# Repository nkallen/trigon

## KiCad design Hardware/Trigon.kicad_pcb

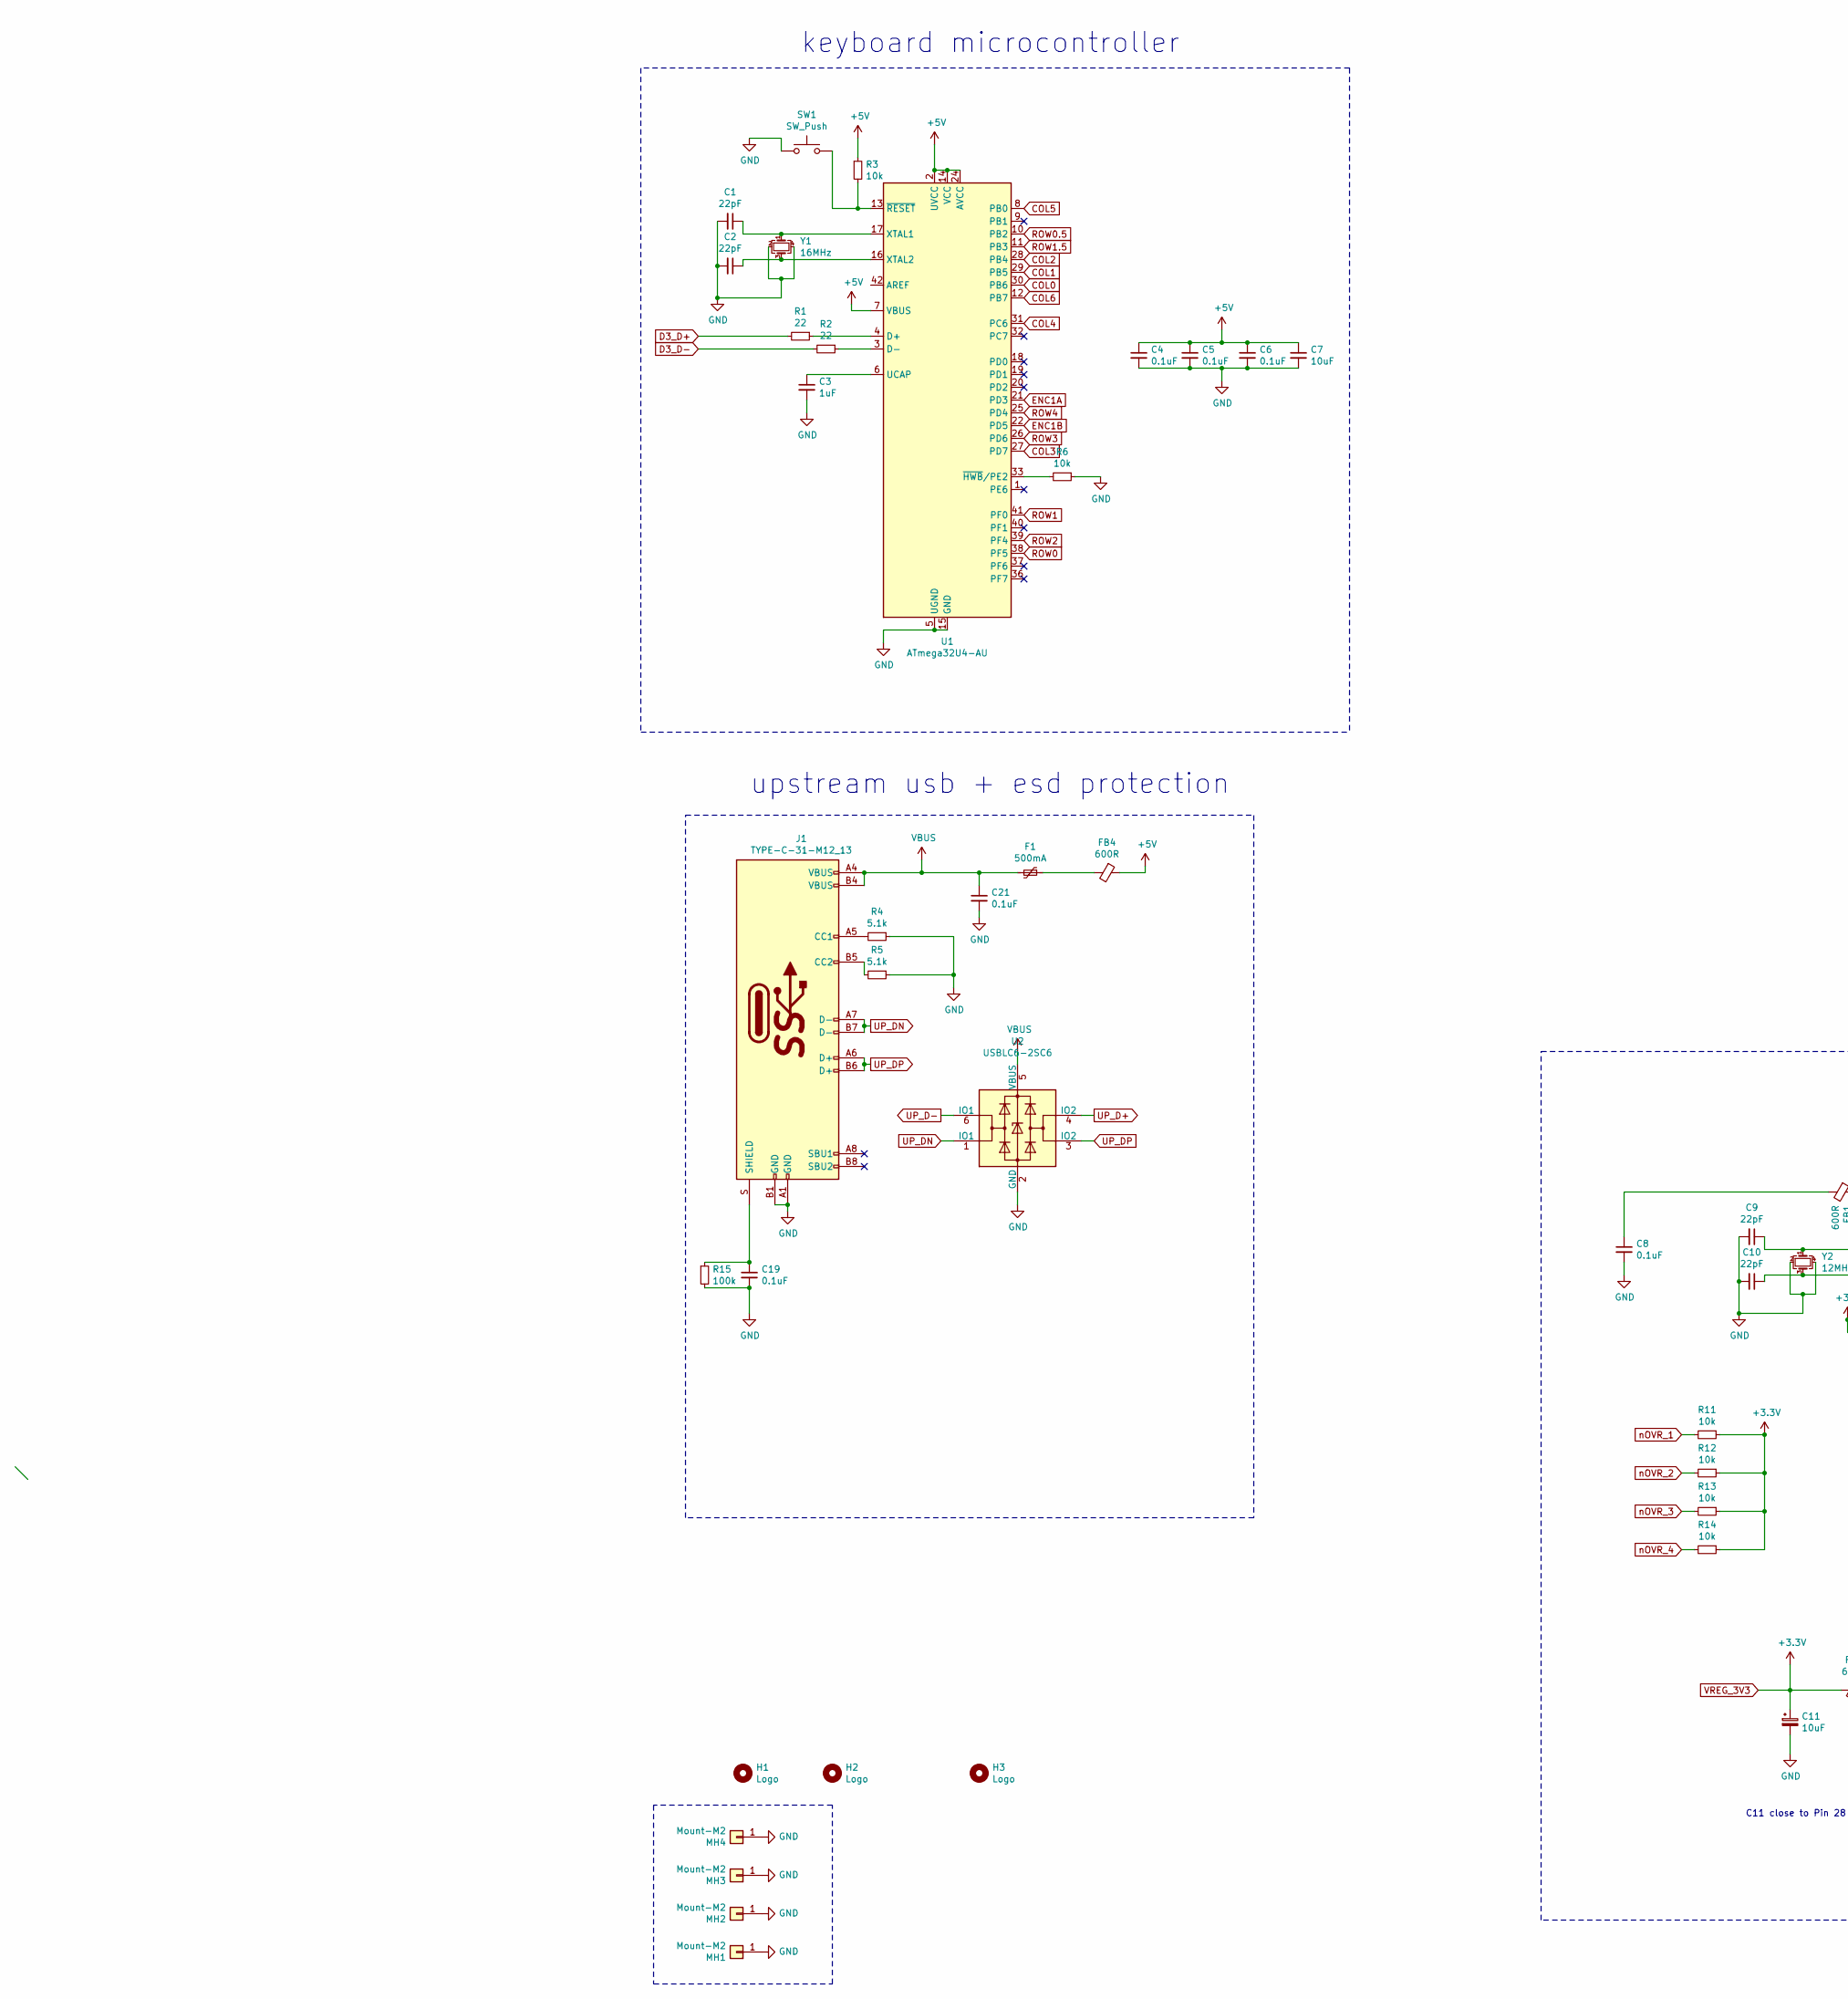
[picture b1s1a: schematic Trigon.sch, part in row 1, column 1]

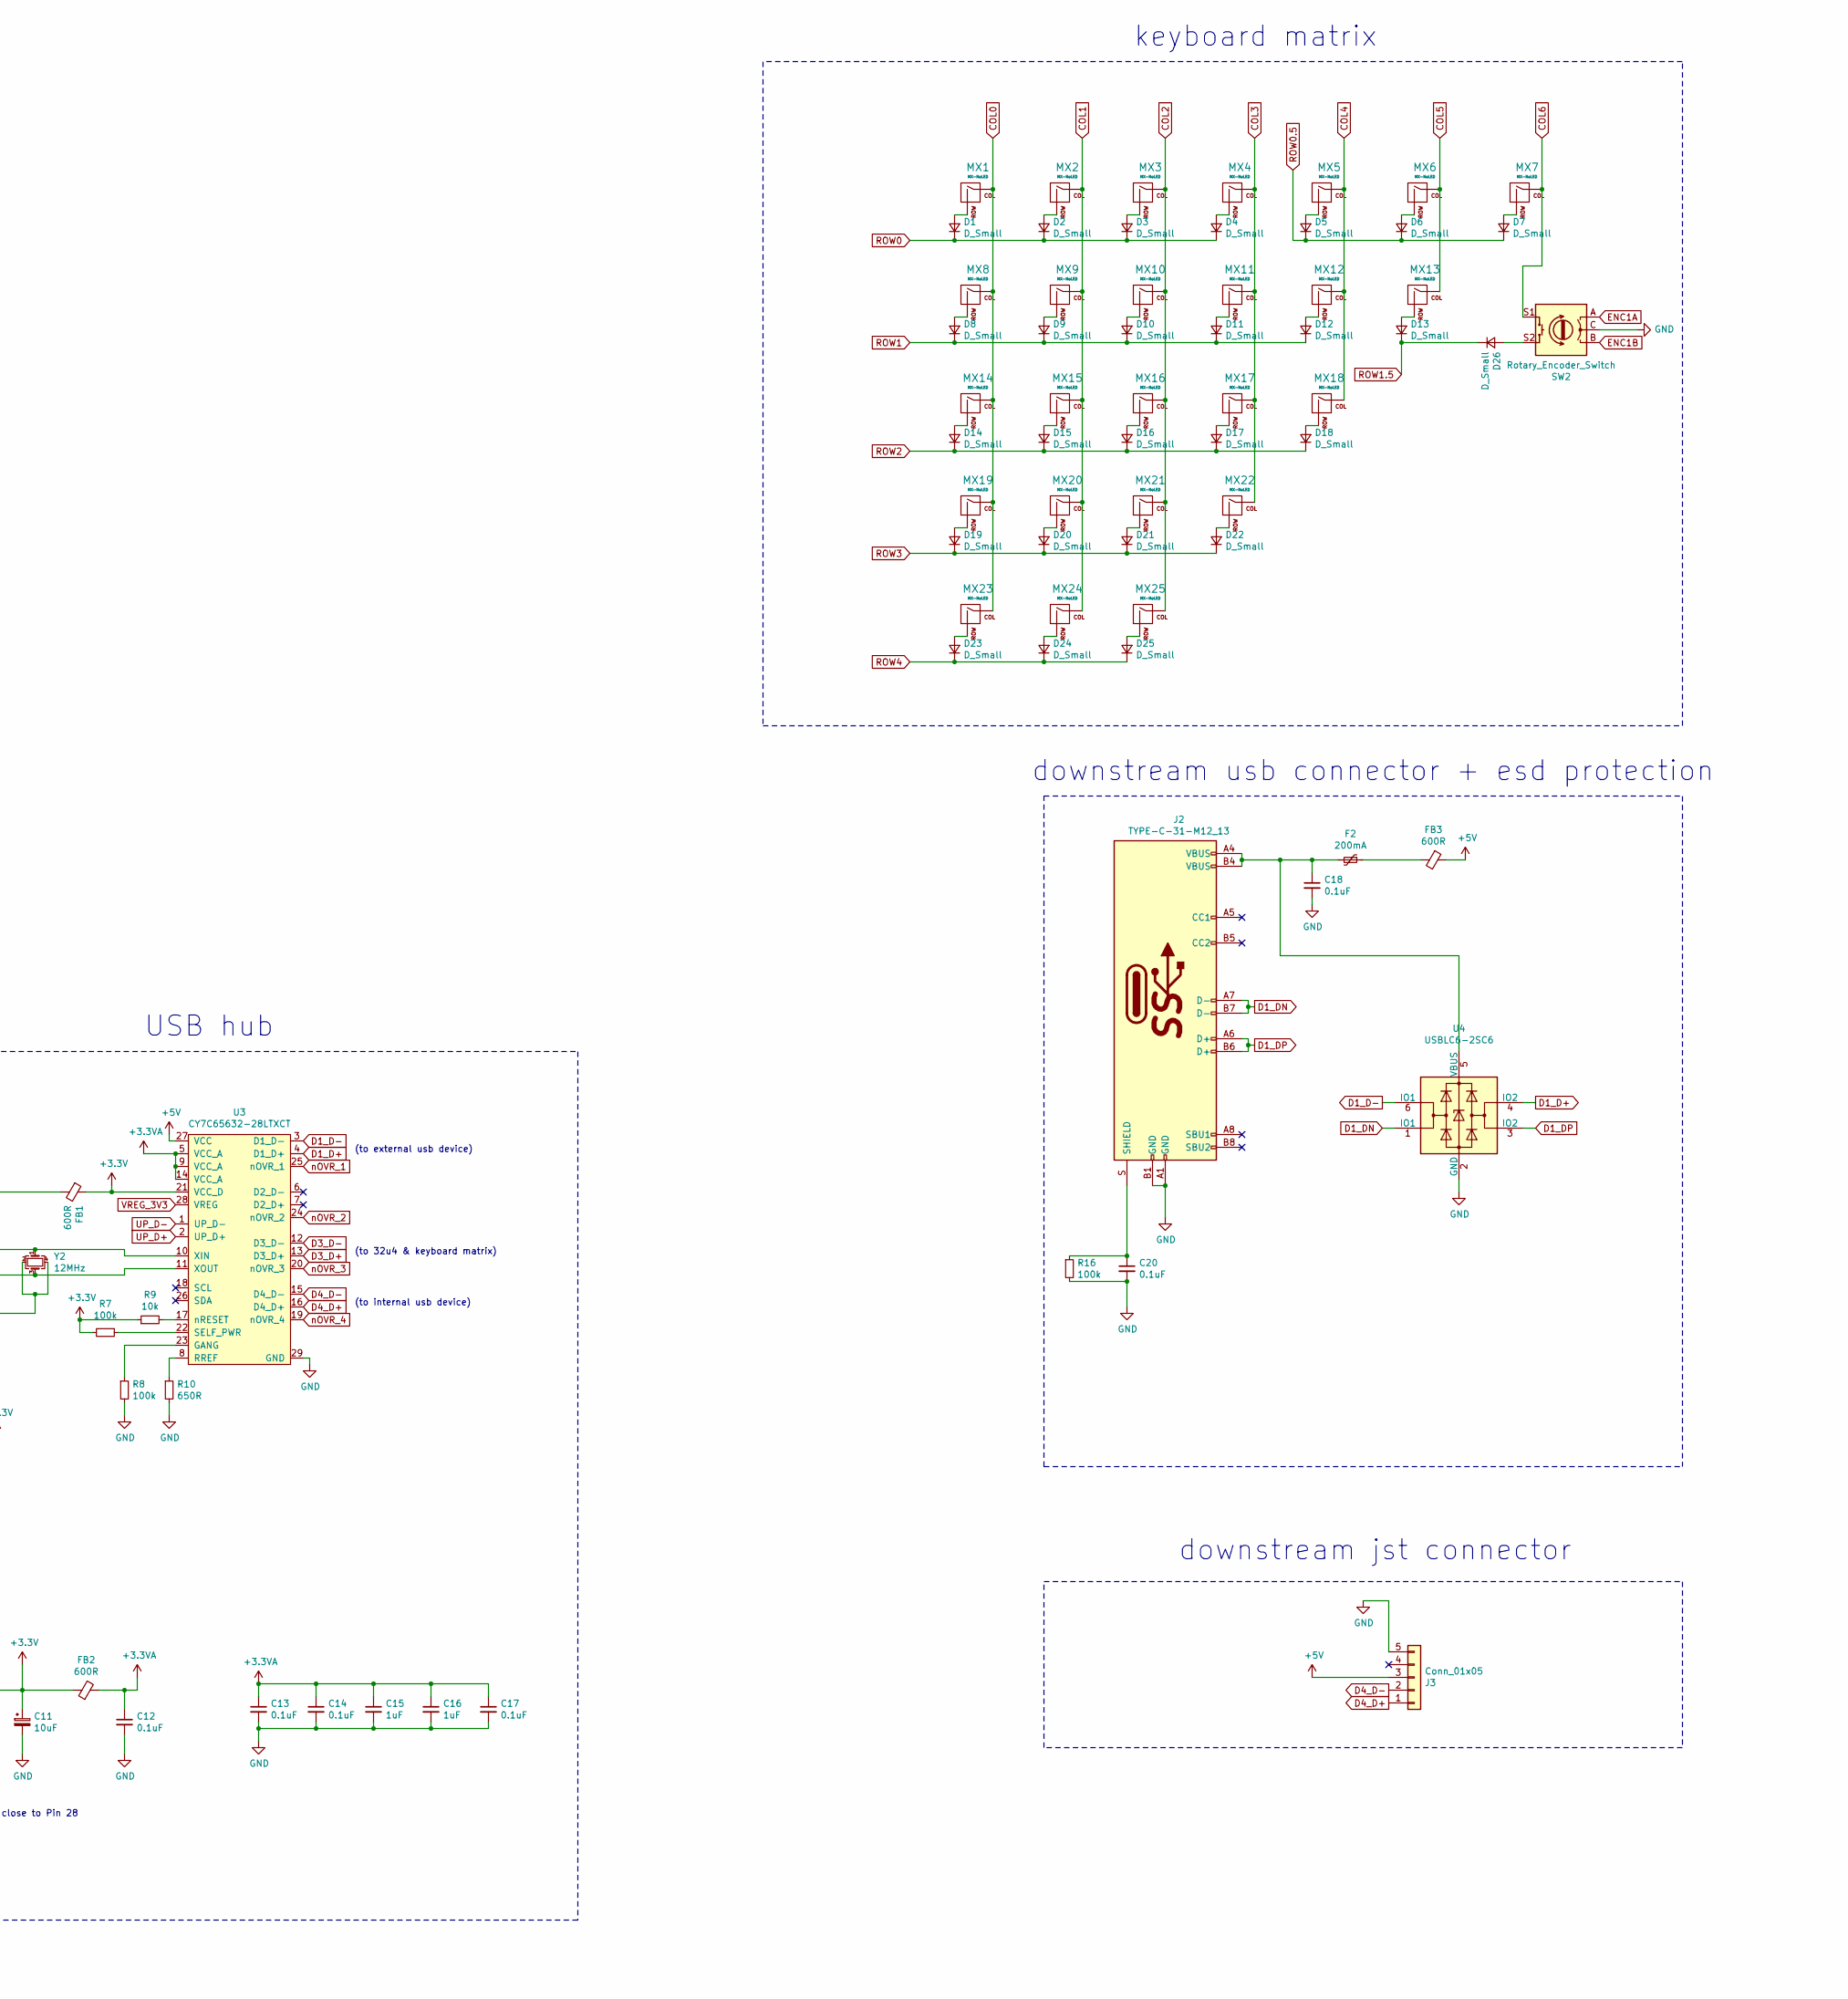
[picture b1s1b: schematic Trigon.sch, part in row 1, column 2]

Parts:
C1, C2, C9, C10: 22pF; C_0603_1608Metric; Manufacturer Part # CL10C220JB8NNNC
C3, C15, C16: 1uF; C_0603_1608Metric; Manufacturer Part # CL10A105KB8NNNC
C4, C5, C6, C8, C12, C13, C14, C17, C18, C19, C20, C21: 0.1uF; C_0603_1608Metric; Manufacturer Part # CC0603KRX7R9BB104
C7, C11: 10uF; C_0603_1608Metric; Manufacturer Part # CL10A106KP8NNNC
D1, D2, D3, D4, D5, D6, D7, D8, D9, D10, D11, D12, D13, D14, D15, D16, D17, D18, D19, D20, D21, D22, D23, D24, D25, D26: D_Small; D_SOD-123; Manufacturer Part # 1N4148W
F1: 500mA; Fuse_1206_3216Metric; Manufacturer Part # 1206L050YR
F2: 200mA; Fuse_1206_3216Metric; Manufacturer Part # 1206L020YR
FB1, FB2, FB3, FB4: 600R; Ferrite_Bead_0603; Manufacturer Part # BLM18AG601SN1D
H1: Logo; wiggle
H2: Logo; back
H3: Logo; backside
J1, J2: TYPE-C-31-M12_13; TYPE-C-31-M-12; Manufacturer Part # TYPE-C-31-M-12
J3: Conn_01x05; JST_SH_SM05B-SRSS-TB_1x05-1MP_P1.00mm_Horizontal; Manufacturer Part # SM05B-SRSS-TB(LF)(SN)
MH1, MH2, MH3, MH4: Mount-M2; MountingHole_3.2mm_M3_Pad_v2
MX1, MX2, MX3, MX4, MX5, MX6, MX7, MX8, MX9, MX10, MX11, MX12, MX13, MX14, MX15, MX16, MX17, MX18, MX19, MX20, MX21, MX22, MX23, MX24, MX25: MX-NoLED; Kailh_Hotswap_1U
R1, R2: 22; R_0603_1608Metric; Manufacturer Part # 0603WAF220JT5E
R3, R6, R9, R11, R12, R13, R14: 10k; R_0603_1608Metric; Manufacturer Part # 0603WAF1002T5E
R4, R5: 5.1k; R_0603_1608Metric; Manufacturer Part # 0603WAF5101T5E
R7, R8, R15, R16: 100k; R_0603_1608Metric; Manufacturer Part # 0603WAF1003T5E
R10: 650R; R_0603_1608Metric; Manufacturer Part # 0603WAF6490T5E
SW1: SW_Push; SKQG-1155865; Manufacturer Part # TS-1187A-B-A-B
SW2: Rotary_Encoder_Switch; RotaryEncoder_Alps_EC11E-Switch_Vertical_H20mm
U1: ATmega32U4-AU; TQFP-44_10x10mm_P0.8mm; Manufacturer Part # ATMEGA32U4-AU
U2, U4: USBLC6-2SC6; SOT-23-6; Manufacturer Part # USBLC6-2SC6
U3: CY7C65632-28LTXCT; QFN-28-1EP_5x5mm_P0.5mm_EP3.35x3.35mm_ThermalVias; Manufacturer Part # CY7C65632-28LTXCT
Y1: 16MHz; Crystal_SMD_3225-4Pin_3.2x2.5mm; Manufacturer Part # X322516MRB4SI
Y2: 12MHz; Crystal_SMD_3225-4Pin_3.2x2.5mm; Manufacturer Part # X322512MSB4SI

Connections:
+3.3VA: C12.1, C13.1, C14.1, C15.1, C16.1, C17.1, FB2.2, U3.5 (VCC_A), U3.9 (VCC_A), U3.14 (VCC_A)
+5V: C4.1, C5.1, C6.1, C7.1, FB3.1, FB4.1, J3.3, R3.1, U1.2 (UVCC), U1.7 (VBUS), U1.14 (VCC), U1.24 (AVCC), U1.34 (VCC), U1.44 (AVCC), U3.27 (VCC)
COL0: MX1.1 (COL), MX8.1 (COL), MX14.1 (COL), MX19.1 (COL), MX23.1 (COL), U1.30 (PB6)
COL1: MX2.1 (COL), MX9.1 (COL), MX15.1 (COL), MX20.1 (COL), MX24.1 (COL), U1.29 (PB5)
COL2: MX3.1 (COL), MX10.1 (COL), MX16.1 (COL), MX21.1 (COL), MX25.1 (COL), U1.28 (PB4)
COL3: MX4.1 (COL), MX11.1 (COL), MX17.1 (COL), MX22.1 (COL), U1.27 (PD7)
COL4: MX5.1 (COL), MX12.1 (COL), MX18.1 (COL), U1.31 (PC6)
COL5: MX6.1 (COL), MX13.1 (COL), U1.8 (PB0)
COL6: MX7.1 (COL), SW2.S1, U1.12 (PB7)
D1_D+: U3.4 (D1_D+), U4.4 (IO2)
D1_D-: U3.3 (D1_D-), U4.6 (IO1)
D1_DN: J2.A7 (D-), J2.B7 (D-), U4.1 (IO1)
D1_DP: J2.A6 (D+), J2.B6 (D+), U4.3 (IO2)
D3_D+: R1.2, U3.13 (D3_D+)
D3_D-: R2.2, U3.12 (D3_D-)
D4_D+: J3.1, U3.16 (D4_D+)
D4_D-: J3.2, U3.15 (D4_D-)
ENC1A: SW2.A, U1.21 (PD3)
ENC1B: SW2.B, U1.22 (PD5)
GND: C1.2, C2.2, C3.2, C4.2, C5.2, C6.2, C7.2, C8.2, C9.2, C10.2, C11.2, C12.2, C13.2, C14.2, C15.2, C16.2, C17.2, C18.2, C19.2, C20.2, C21.2, J1.A1 (GND), J1.B1 (GND), J2.A1 (GND), J2.B1 (GND), J3.5, MH1.1, MH2.1, MH3.1, MH4.1, R4.1, R5.1, R6.1, R8.2, R10.2, R15.2, R16.2, SW1.1, SW2.C, U1.5 (UGND), U1.15 (GND), U1.23 (GND), U1.35 (GND), U1.43 (GND), U2.2 (GND), U3.29 (GND), U4.2 (GND), Y1.2, Y1.4, Y2.2, Y2.4
unnamed: C1.1, U1.17 (XTAL1), Y1.1
unnamed: C2.1, U1.16 (XTAL2), Y1.3
unnamed: C3.1, U1.6 (UCAP)
unnamed: C8.1, FB1.2
unnamed: C9.1, U3.10 (XIN), Y2.1
unnamed: C10.1, U3.11 (XOUT), Y2.3
unnamed: C18.1, F2.2, J2.A4 (VBUS), J2.B4 (VBUS), U4.5 (VBUS)
unnamed: C19.1, J1.S (SHIELD), R15.1
unnamed: C20.1, J2.S (SHIELD), R16.1
unnamed: D1.2 (A), MX1.2 (ROW)
unnamed: D2.2 (A), MX2.2 (ROW)
unnamed: D3.2 (A), MX3.2 (ROW)
unnamed: D4.2 (A), MX4.2 (ROW)
unnamed: D5.2 (A), MX5.2 (ROW)
unnamed: D6.2 (A), MX6.2 (ROW)
unnamed: D7.2 (A), MX7.2 (ROW)
unnamed: D8.2 (A), MX8.2 (ROW)
unnamed: D9.2 (A), MX9.2 (ROW)
unnamed: D10.2 (A), MX10.2 (ROW)
unnamed: D11.2 (A), MX11.2 (ROW)
unnamed: D12.2 (A), MX12.2 (ROW)
unnamed: D13.2 (A), MX13.2 (ROW)
unnamed: D14.2 (A), MX14.2 (ROW)
unnamed: D15.2 (A), MX15.2 (ROW)
unnamed: D16.2 (A), MX16.2 (ROW)
unnamed: D17.2 (A), MX17.2 (ROW)
unnamed: D18.2 (A), MX18.2 (ROW)
unnamed: D19.2 (A), MX19.2 (ROW)
unnamed: D20.2 (A), MX20.2 (ROW)
unnamed: D21.2 (A), MX21.2 (ROW)
unnamed: D22.2 (A), MX22.2 (ROW)
unnamed: D23.2 (A), MX23.2 (ROW)
unnamed: D24.2 (A), MX24.2 (ROW)
unnamed: D25.2 (A), MX25.2 (ROW)
unnamed: D26.2 (A), SW2.S2
unnamed: F1.1, FB4.2
unnamed: F2.1, FB3.2
unnamed: J1.A5 (CC1), R4.2
unnamed: J1.B5 (CC2), R5.2
unnamed: R1.1, U1.4 (D+)
unnamed: R2.1, U1.3 (D-)
unnamed: R3.2, SW1.2, U1.13 (~RESET)
unnamed: R6.2, U1.33 (~HWB~/PE2)
unnamed: R7.1, U3.22 (SELF_PWR)
unnamed: R8.1, U3.23 (GANG)
unnamed: R9.2, U3.17 (nRESET)
unnamed: R10.1, U3.8 (RREF)
ROW0: D1.1 (K), D2.1 (K), D3.1 (K), D4.1 (K), U1.38 (PF5)
ROW0.5: D5.1 (K), D6.1 (K), D7.1 (K), U1.10 (PB2)
ROW1: D8.1 (K), D9.1 (K), D10.1 (K), D11.1 (K), D12.1 (K), U1.41 (PF0)
ROW1.5: D13.1 (K), D26.1 (K), U1.11 (PB3)
ROW2: D14.1 (K), D15.1 (K), D16.1 (K), D17.1 (K), D18.1 (K), U1.39 (PF4)
ROW3: D19.1 (K), D20.1 (K), D21.1 (K), D22.1 (K), U1.26 (PD6)
ROW4: D23.1 (K), D24.1 (K), D25.1 (K), U1.25 (PD4)
UP_D+: U2.4 (IO2), U3.2 (UP_D+)
UP_D-: U2.6 (IO1), U3.1 (UP_D-)
UP_DN: J1.A7 (D-), J1.B7 (D-), U2.1 (IO1)
UP_DP: J1.A6 (D+), J1.B6 (D+), U2.3 (IO2)
VBUS: C21.1, F1.2, J1.A4 (VBUS), J1.B4 (VBUS), U2.5 (VBUS)
VREG_3V3: C11.1, FB1.1, FB2.1, R7.2, R9.1, R11.1, R12.1, R13.1, R14.1, U3.21 (VCC_D), U3.28 (VREG)
nOVR_1: R11.2, U3.25 (nOVR_1)
nOVR_2: R12.2, U3.24 (nOVR_2)
nOVR_3: R13.2, U3.20 (nOVR_3)
nOVR_4: R14.2, U3.19 (nOVR_4)

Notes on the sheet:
(to 32u4 & keyboard matrix)
(to internal usb device)
(to external usb device)
C11 close to Pin 28
keyboard matrix
keyboard microcontroller
upstream usb + esd protection
USB hub
downstream usb connector + esd protection
downstream jst connector

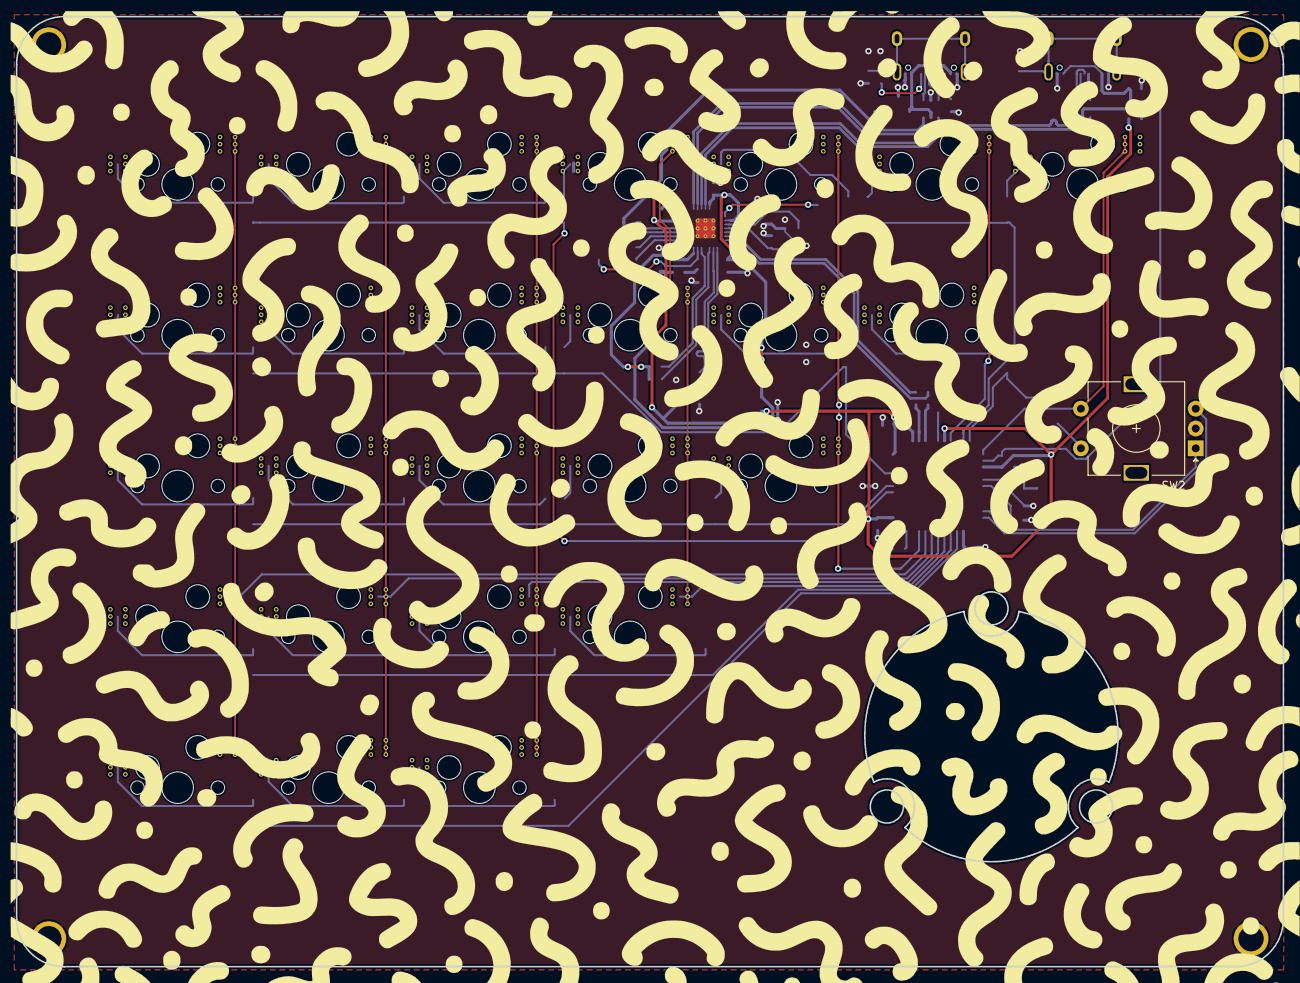
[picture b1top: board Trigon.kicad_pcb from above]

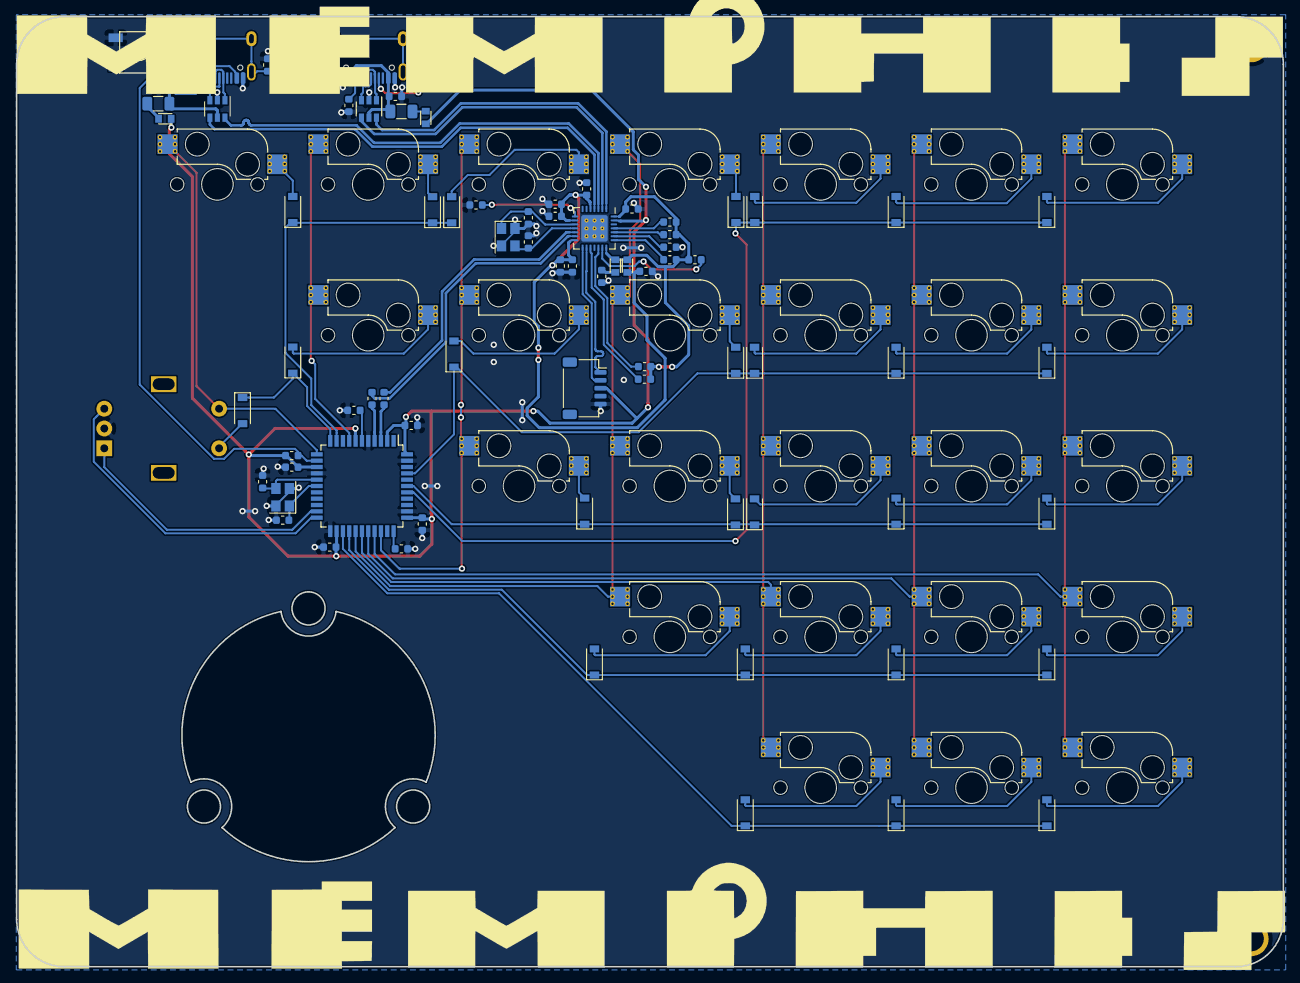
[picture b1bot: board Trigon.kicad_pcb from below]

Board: 2 copper layers, 160.0 x 120.0 mm, 112 parts (109 on the bottom side), 84 nets.

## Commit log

2020-07-08 Submodules
2020-07-08 Libraries
2020-07-08 ProMicro pretty
2020-07-08 ProMicro etc
2020-07-08 Fully laid out board
2020-07-08 dxf files
2020-07-09 onboard usb c
2020-07-10 routed without rows cols
2020-07-10 fully routed matrix
2020-07-10 incorporate feedback
2020-07-10 full ground fill
2020-07-10 decorative stuff
2020-07-11 all on one side
2020-07-11 bring back masq
2020-07-12 cleaning up ground plane for solder mask layer
2020-07-12 new usb connector'
2020-07-13 latest
2020-08-10 Checkpoint
2020-08-11 USB hub
2020-08-12 usb hub pcb layout
2020-08-12 changes to fuse values per joshajohnson
2020-08-13 More compact layout
2020-08-13 incorporating josh's feedback
2020-08-14 next round of feedback from josh
2020-08-14 - Introduced JST connector - Made all D+/D- 14mm thick (max thickness that was easy to deal with) - Added logo / decoration / version #
2020-08-14 Reorganized files
2020-08-14 Removed unnecessary submodules
2020-08-14 Case info
2020-08-15 minor tweaks to layout
2020-08-15 crystal load
2020-08-15 more space for usb
2020-08-15 Gerbers
2020-08-15 min track width
2020-08-15 some via weirdness
2020-08-15 Pad size of U3.29 was too small
2020-08-15 Addressing pcbway complaints of min track width
2020-08-16 New layout
2020-08-17 Latest bom/gerbers; reflecting more of josh's comments
2020-09-10 Checkin
2020-09-10 introducing new naming convention for case
2020-09-10 Mount
2020-09-11 Updates to case
2020-09-24 add html bom
2020-10-06 kailh hotswap switches ;now using a fixed acheron
2020-10-25 using hotswaps
2020-11-10 Cleanup of incorrect pins
2021-04-19 lots of changes
2021-04-20 preping for pcbway
